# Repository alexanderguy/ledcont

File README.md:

# Dimming LED Controller

This is a basic dimming LED controller, designed for being run from one or more batteries (~3.25-6 volts).  It includes:

- Analog dimming.
- Low-voltage shutdown.
- Able to run at up to 1A.
- Two-layer board.

It takes about 1.5 hours to assemble if you're: building your first board, finding parts in the process, binging The Americans.

# Modifications

There are a number of modifications possible:

- Change R4/R7 to provide the low-voltage shutdown point.
- Tune RV2/R10 to tweak the feedback offset.
- Set maximum current via R9 (see PAM2804 datasheet for more information).
- Don't populate D2/U2/RV1 (and supporting components) if dimming isn't needed (pull-up on EN needed).

# Wiring

1. Make sure the switching potentiometer is turned off (i.e past the switch detent, counter-clockwise).
2. Attach your LED(s) to J2 Pin 1/+ and J2 Pin 2/-.
3. Attach your power supply to J1 Pin 1/+ and J1 Pin 2/-.

# Dimming Setup

1. Turn the potentiometer on, just past the switch detent.
2. Turn the potentiometer the opposite direction, until resistance is felt.  The LEDs might turn off.
3. If the LEDs are off, adjust RV2 until they are on.
4. If the LEDs were off, adjust RV2 until they just barely turn on.
5. Verify that the potentiometer now gives you complete brightness range for your LEDs.

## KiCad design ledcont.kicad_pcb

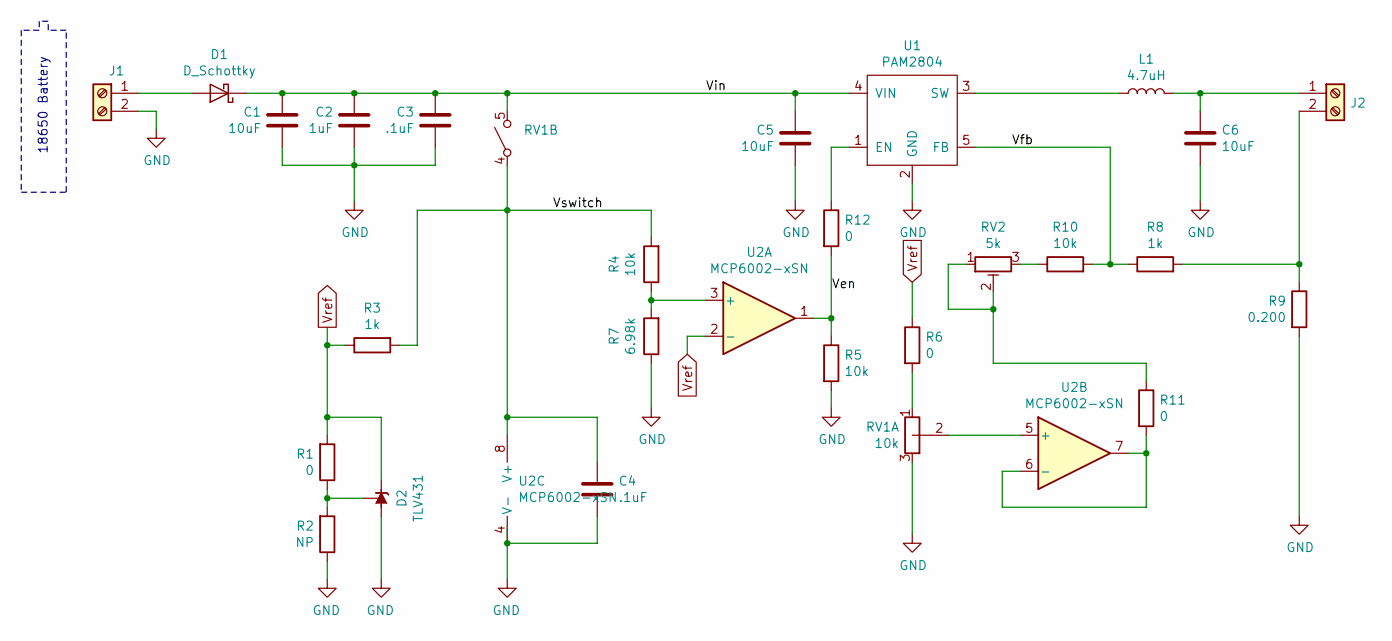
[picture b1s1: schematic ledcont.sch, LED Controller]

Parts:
C1, C5, C6: 10uF; C_1206_3216Metric_Pad1.42x1.75mm_HandSolder; Part CL31B106KOHNFNE
C2: 1uF; C_1206_3216Metric_Pad1.42x1.75mm_HandSolder; Part CL31B105MAHNNNE
C3, C4: .1uF; C_1206_3216Metric_Pad1.42x1.75mm_HandSolder; Part CL31B104KBCNNNC
D1: D_Schottky; D_SOD-123F; Part NRVTS245ESFT1G
D2: TLV431; SOT-23
J1, J2: Screw_Terminal_01x02; TerminalBlock_Phoenix_PT-1,5-2-3.5-H_1x02_P3.50mm_Horizontal; Part 1984617
L1: 4.7uH; L_1812_4532Metric_Pad1.30x3.40mm_HandSolder; Part LQH43PN4R7M26L
R1: 0; R_0603_1608Metric_Pad1.05x0.95mm_HandSolder; Tolerance 1%; Part RC0603FR-070RL
R2: NP; R_0603_1608Metric_Pad1.05x0.95mm_HandSolder; Tolerance 1%
R3: 1k; R_0603_1608Metric_Pad1.05x0.95mm_HandSolder; Tolerance 1%; Part RC0603FR-071KL
R4, R5, R10: 10k; R_0603_1608Metric_Pad1.05x0.95mm_HandSolder; Tolerance 1%; Part RC0603FR-0710KL
R6, R11, R12: 0; R_0603_1608Metric_Pad1.05x0.95mm_HandSolder; Part RC0603FR-070RL
R7: 6.98k; R_0603_1608Metric_Pad1.05x0.95mm_HandSolder; Tolerance 1%; Part RC0603FR-076K98L
R8: 1k; R_1206_3216Metric_Pad1.42x1.75mm_HandSolder; Tolerance 1%; Part RC1206FR-071KL
R9: 0.200; R_1206_3216Metric_Pad1.42x1.75mm_HandSolder; Tolerance 1%; Part PT1206FR-070R2L
RV1: 10k; P091_S; Part P091S-FC20BR10K
RV2: 5k; TC33X
U1: PAM2804; TSOT-23-5_HandSoldering; Part PAM2804AAB010
U2: MCP6002-xSN; SOIC-8_3.9x4.9mm_P1.27mm

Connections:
/Ven: R5.1, R12.2, U2.1
/Vfb: R8.1, R10.2, U1.5 (FB)
/Vin: C1.1, C2.1, C3.1, C5.1, D1.1 (K), RV1.5, U1.4 (VIN)
/Vswitch: C4.1, R3.2, R4.2, RV1.4, U2.8 (V+)
GND: C1.2, C2.2, C3.2, C4.2, C5.2, C6.2, D2.3 (A), J1.2, R2.1, R5.2, R7.1, R9.2, RV1.3, U1.2 (GND), U2.4 (V-)
unnamed: C6.1, J2.1, L1.2
unnamed: D1.2 (A), J1.1
unnamed: D2.2 (REF), R1.1, R2.2
unnamed: J2.2, R8.2, R9.1
unnamed: L1.1, U1.3 (SW)
unnamed: R4.1, R7.2, U2.3 (+)
unnamed: R6.2, RV1.1
unnamed: R10.1, RV2.3
unnamed: R11.1, RV2.1, RV2.2
unnamed: R11.2, U2.6 (-), U2.7
unnamed: R12.1, U1.1 (EN)
unnamed: RV1.2 (B), U2.5 (+)
Vref: D2.1 (K), R1.2, R3.1, R6.1, U2.2 (-)

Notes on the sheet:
18650 Battery

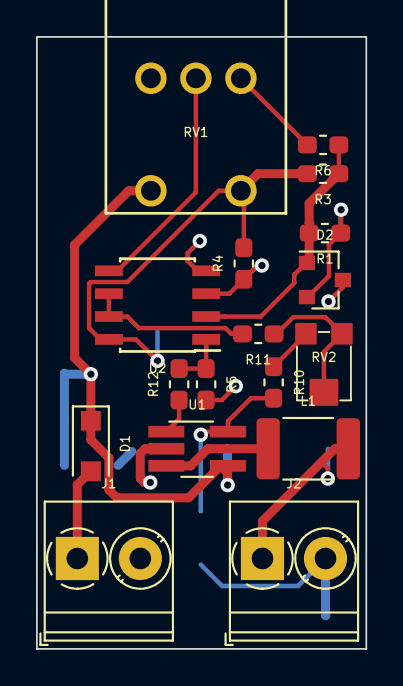
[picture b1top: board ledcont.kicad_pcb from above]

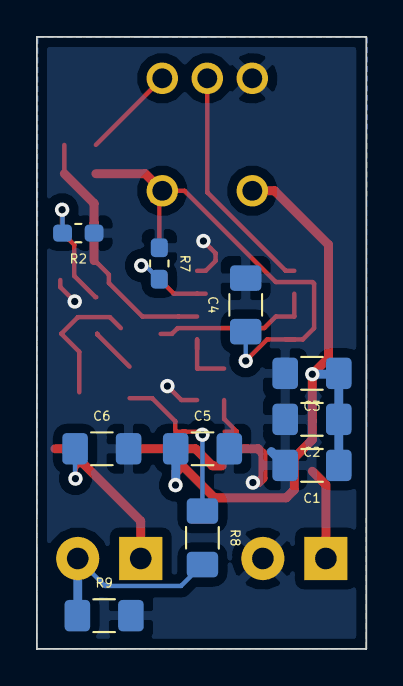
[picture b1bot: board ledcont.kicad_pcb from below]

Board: 2 copper layers, 18.3 x 34.0 mm, 27 parts (10 on the bottom side), 18 nets.

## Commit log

2019-01-10 Added ignores.
2019-01-11 Created a KiCad project.
2019-01-12 Continued work on the schematic.
2019-01-12 Started working on a bill of materials.
2019-01-22 Updated to the latest and greatest.
2019-01-22 More parts.
2019-01-22 New footprint for PAM2804.
2019-01-22 Assigned footprints.
2019-01-22 More progress.
2019-01-22 Updated footprints.
2019-01-22 Checkpoint before real board layout.
2019-01-23 Added courtyard.
2019-01-23 Finished first attempt at board layout.
2019-01-23 Board cutout. Rewired unused comparator.
2019-01-28 Reverse potentionmeter usage so that the LEDs start out dimmed.
2019-01-28 Remove this note.
2019-01-29 Switched PAM2804 to a standard TSOT-23-5 footprint.
2019-01-29 Regenerated net file.
2019-01-29 Remove our custom local footprint.
2019-01-29 Remove this old library.
2019-02-07 Start transitioning to lower-voltage parts.
2019-02-08 Added the TC33X trimmer pot footprint.
2019-02-08 More board updates.
2019-02-08 More work to get things ordered. Updated the BoM.
2019-02-08 Updated the schematic. Fixed missing PNs.
2019-02-17 Brought some of these from the kicad release so we can tweak them.
2019-02-17 Commit this generated output for ease of use.
2019-02-17 Added README.
2019-02-17 Provide a schematic preview.
2019-02-17 Embed the schematic image.
2019-02-17 Compensate for D1's forward drop.
2019-02-17 Add part vendors.
2019-03-06 Add images.
2019-03-06 Fix vendors.
2019-04-02 Rename.
